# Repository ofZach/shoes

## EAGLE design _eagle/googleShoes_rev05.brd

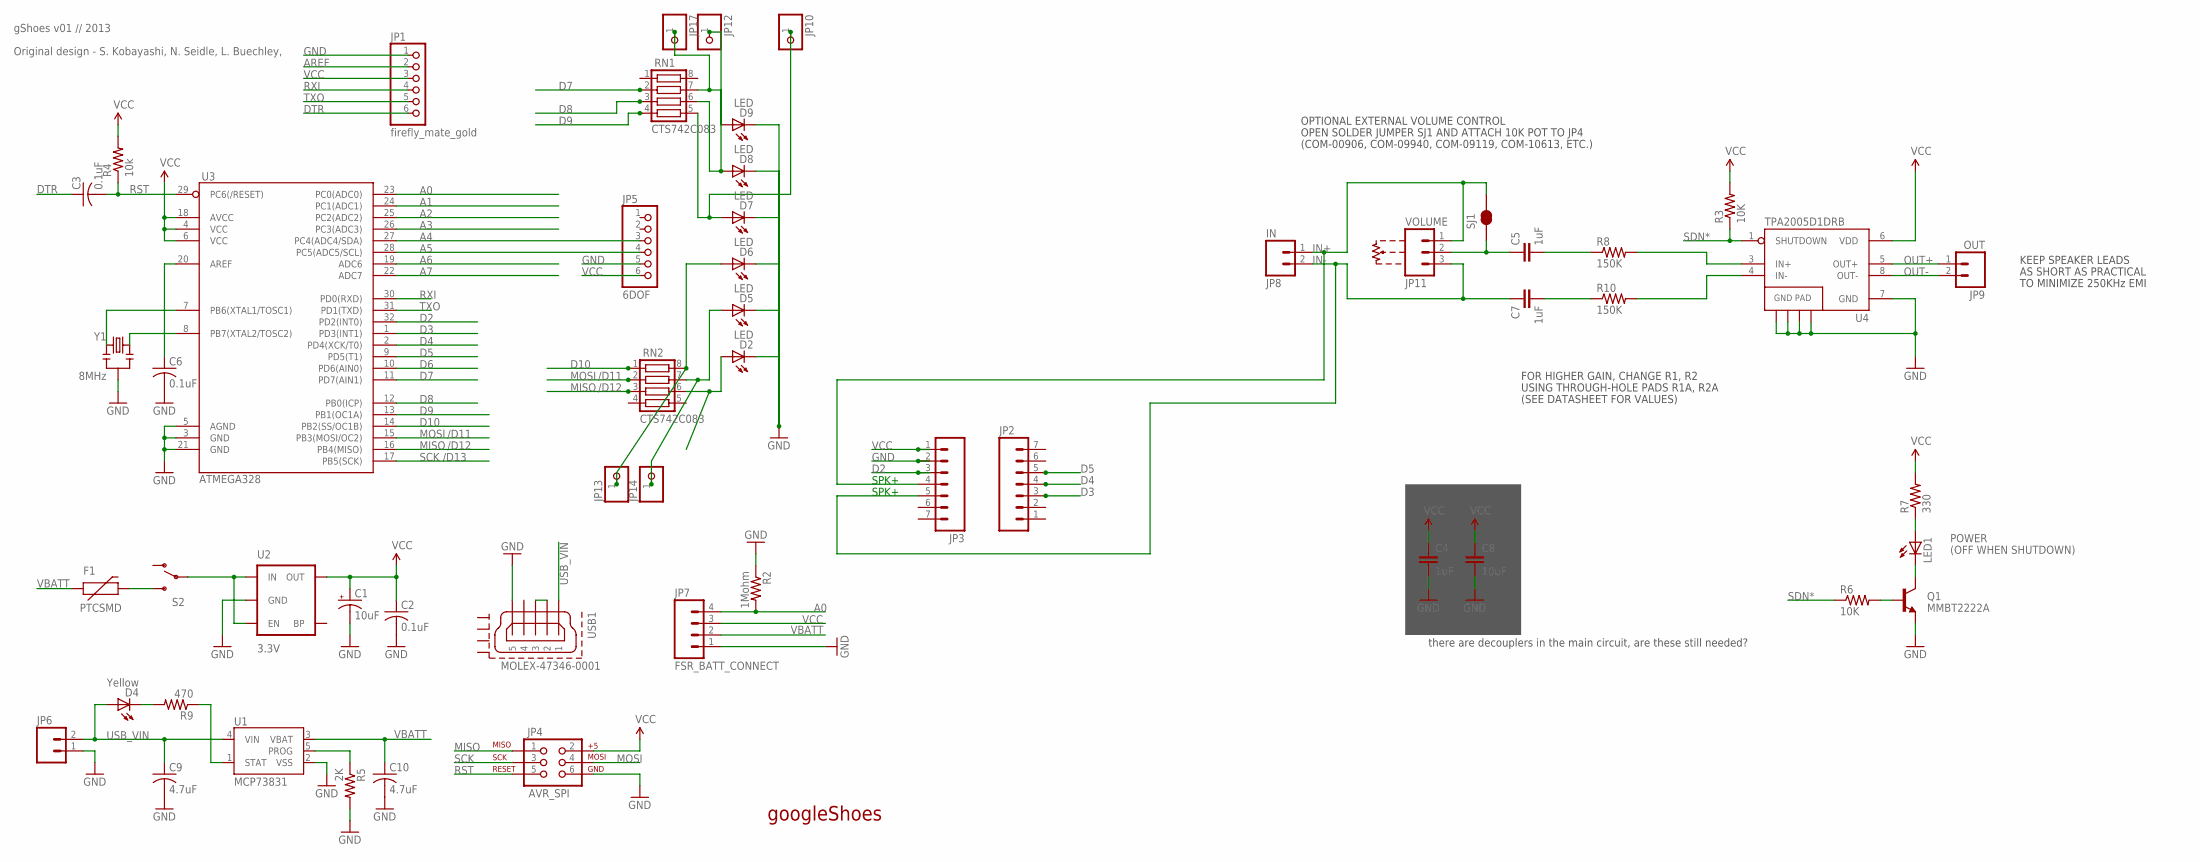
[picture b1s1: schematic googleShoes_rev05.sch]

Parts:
C1: 10uF; EIA3216
C2, C3, C6: 0.1uF; C0805
C4, C5, C7: 1uF; 1206
C8: 10uF; 1206
C9, C10: 4.7uF; C0805
D2, D5, D6, D7, D8, D9: LED; CHIP-LED0805
D4: Yellow; CHIP-LED0805
F1: PTCSMD; PTC-1206
JP1: firefly_mate_gold; 1X06-BIG
JP2, JP3: M07; 1X07
JP4: AVR_SPI; 2X3
JP5: 6DOF; 1X06-BIG
JP6: M02PTH; 1X02
JP7: FSR_BATT_CONNECT; 1X04
JP8: IN; 1X02
JP9: OUT; 1X02
JP10, JP12, JP13, JP14, JP17: PINHD-1X1CB; 1X01-CLEANBIG
JP11: VOLUME; 1X03
LED1: LEDCHIPLED_0805; CHIPLED_0805
Q1: MMBT2222A; SOT23-3
R2: 1Mohm; M0805
R3, R6: 10K; M0805
R4: 10k; M0805
R5: 2K; M0805
R7: 330; M0805
R8, R10: 150K; M0805
R9: 470; M0805
RN1, RN2: CTS742C083
S2: SWITCH-SPSTSMD; AYZ0202
SJ1: SOLDERJUMPERNC2; SJ_2S-NOTRACE
U1: MCP73831; SOT23-5
U2: 3.3V; SOT23-5
U3: ATMEGA328; TQFP32-08
U4: TPA2005D1DRB; QFN-8_PAD
USB1: MOLEX-47346-0001; MOLEX-47364-0001
Y1: 8MHz; RESONATOR-SMD

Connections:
A0: JP7.4, R2.2, U3.23 (PC0(ADC0))
A1: U3.24 (PC1(ADC1))
A2: U3.25 (PC2(ADC2))
A3: U3.26 (PC3(ADC3))
A4: JP5.3, U3.27 (PC4(ADC4/SDA))
A5: JP5.4, U3.28 (PC5(ADC5/SCL))
A6: U3.19 (ADC6)
A7: U3.22 (ADC7)
AREF: C6.1, JP1.2, U3.20 (AREF)
D2: JP3.3, U3.32 (PD2(INT0))
D3: JP2.3, U3.1 (PD3(INT1))
D4: JP2.4, U3.2 (PD4(XCK/T0))
D5: JP2.5, U3.9 (PD5(T1))
D6: U3.10 (PD6(AIN0))
D7: RN1.2, U3.11 (PD7(AIN1))
D8: RN1.3, U3.12 (PB0(ICP))
D9: RN1.4, U3.13 (PB1(OC1A))
D10: RN2.1, U3.14 (PB2(SS/OC1B))
DTR: C3.1, JP1.6
GND: C1.C (-), C2.2, C4.2, C6.2, C8.2, C9.2, C10.2, D2.C, D5.C, D6.C, D7.C, D8.C, D9.C, JP1.1, JP3.2, JP4.6, JP5.5, JP6.1, JP7.1, Q1.2 (E), R2.1, R5.2, U1.2 (VSS), U2.2 (GND), U3.3 (GND), U3.5 (AGND), U3.21 (GND), U4.7 (GND), U4.10 (GND), U4.11 (GND), U4.12 (GND), U4.13 (GND), USB1.5, Y1.2
IN+: JP3.4, JP8.1, JP11.1, SJ1.2
IN+AMP: R8.2, U4.3 (IN+)
IN-: C7.1, JP3.5, JP8.2, JP11.3
IN-AMP: R10.2, U4.4 (IN-)
MISO: JP4.1, RN2.3, U3.16 (PB4(MISO))
MOSI: JP4.4, RN2.2, U3.15 (PB3(MOSI/OC2))
unnamed: C5.1, JP11.2, SJ1.1
unnamed: D5.A, JP14.1, RN2.7
unnamed: D2.A, RN2.6
unnamed: S2.2, U2.1 (IN), U2.3 (EN)
unnamed: D6.A, JP13.1, RN2.8
unnamed: D4.C, R9.2
unnamed: F1.2, S2.3 (S)
unnamed: U3.7 (PB6(XTAL1/TOSC1)), Y1.3
unnamed: R5.1, U1.5 (PROG)
unnamed: U3.8 (PB7(XTAL2/TOSC2)), Y1.1
unnamed: R9.1, U1.1 (STAT)
unnamed: D9.A, JP17.1, RN1.7
unnamed: D8.A, JP12.1, RN1.6
unnamed: D7.A, JP10.1, RN1.5
unnamed: LED1.A, R7.1
unnamed: Q1.1 (B), R6.2
unnamed: LED1.C, Q1.3 (C)
unnamed: C5.2, R8.1
unnamed: C7.2, R10.1
unnamed: USB1.2, USB1.3
OUT+: JP9.1, U4.5 (OUT+)
OUT-: JP9.2, U4.8 (OUT-)
RST: C3.2, JP4.5, R4.1, U3.29 (PC6(/RESET))
RXI: JP1.4, U3.30 (PD0(RXD))
SCK: JP4.3, U3.17 (PB5(SCK))
SDN*: R3.1, R6.1, U4.1 (SHUTDOWN)
TXO: JP1.5, U3.31 (PD1(TXD))
USB_VIN: C9.1, D4.A, JP6.2, U1.4 (VIN), USB1.1
VBATT: C10.1, F1.1, JP7.2, U1.3 (VBAT)
VCC: C1.A (+), C2.1, C4.1, C8.1, JP1.3, JP3.1, JP4.2, JP5.6, JP7.3, R3.2, R4.2, R7.2, U2.5 (OUT), U3.4 (VCC), U3.6 (VCC), U3.18 (AVCC), U4.6 (VDD)

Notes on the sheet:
googleShoes
/D11
/D12
/D13
Original design - S. Kobayashi, N. Seidle, L. Buechley,
gShoes v01 // 2013
SPK+
POWER
(OFF WHEN SHUTDOWN)
OPEN SOLDER JUMPER SJ1 AND ATTACH 10K POT TO JP4
OPTIONAL EXTERNAL VOLUME CONTROL
FOR HIGHER GAIN, CHANGE R1, R2
USING THROUGH-HOLE PADS R1A, R2A
(SEE DATASHEET FOR VALUES)
(COM-00906, COM-09940, COM-09119, COM-10613, ETC.)
KEEP SPEAKER LEADS
AS SHORT AS PRACTICAL
TO MINIMIZE 250KHz EMI
there are decouplers in the main circuit, are these still needed?

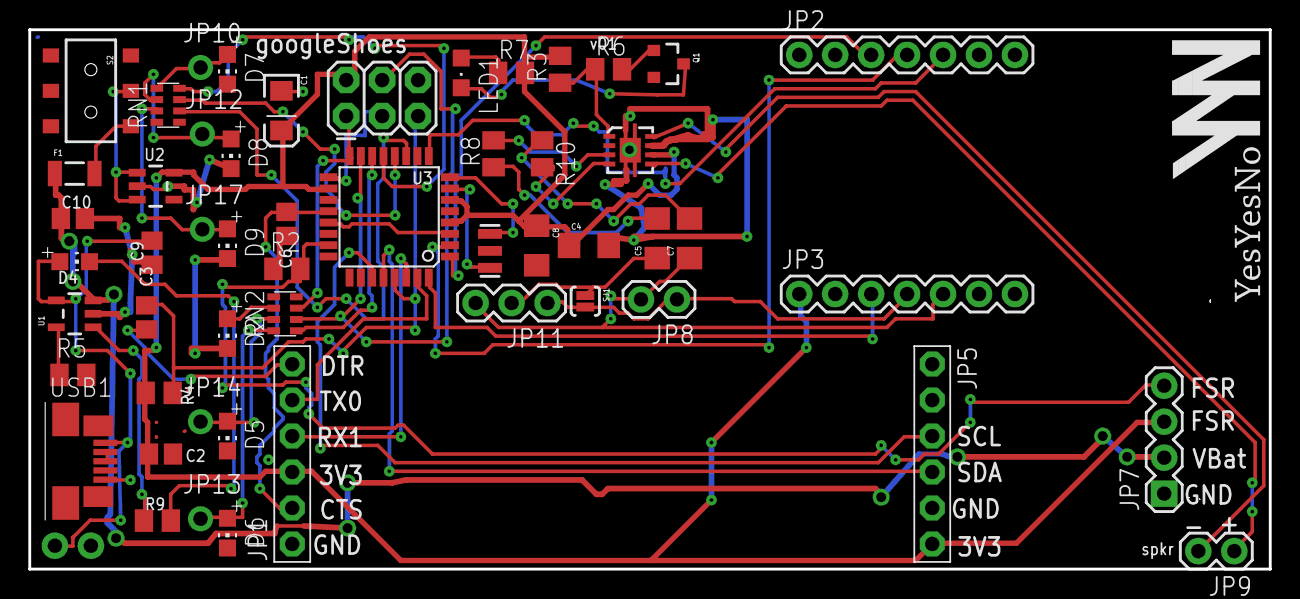
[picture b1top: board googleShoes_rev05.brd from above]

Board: 2 copper layers, 87.6 x 38.1 mm, 54 parts (1 on the bottom side), 50 nets.

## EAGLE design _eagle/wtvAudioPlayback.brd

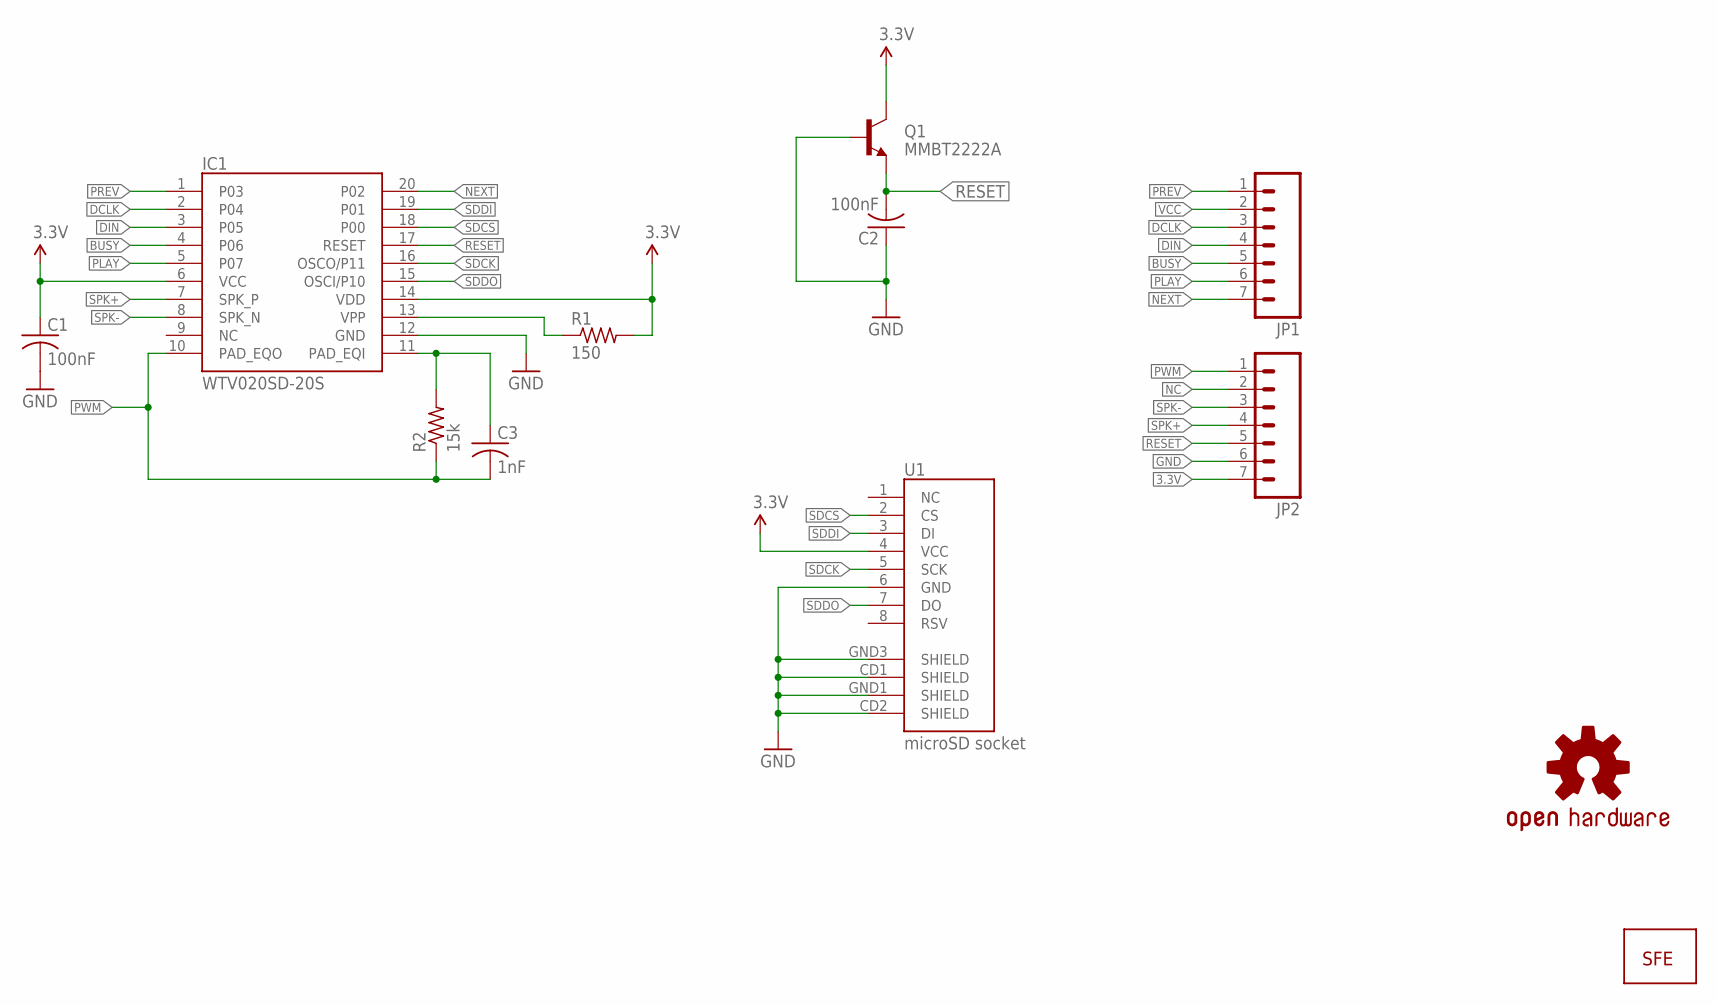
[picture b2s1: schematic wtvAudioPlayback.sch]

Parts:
C1, C2: 100nF; C025-024X044
C3: 1nF; C025-024X044
IC1: WTV020SD-20S; SSOP_20
JP1, JP2: M07; 1X07
JP5: LOGO-SFENEW; SFE-NEW-WEBLOGO
Q1: MMBT2222A; SOT23
R1: 150; 0207/2V
R2: 15k; 0207/2V
U1: microSD socket; MICRO-SD-SOCKET-PP
U$1: OSHW-LOGOS; OSHW-LOGO-S

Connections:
3.3V: C1.1, IC1.6 (VCC), IC1.14 (VDD), JP2.7, Q1.3 (C), R1.2, U1.4 (VCC)
BUSY: IC1.4 (P06), JP1.5
DCLK: IC1.2 (P04), JP1.3
DIN: IC1.3 (P05), JP1.4
GND: C1.2, C2.1, IC1.12 (GND), JP2.6, Q1.1 (B), U1.6 (GND), U1.CD1 (SHIELD), U1.CD2 (SHIELD), U1.GND1 (SHIELD), U1.GND3 (SHIELD)
unnamed: IC1.13 (VPP), R1.1
unnamed: C3.1, IC1.11 (PAD_EQI), R2.2
NC: JP2.2
NEXT: IC1.20 (P02), JP1.7
PLAY: IC1.5 (P07), JP1.6
PREV: IC1.1 (P03), JP1.1
PWM: C3.2, IC1.10 (PAD_EQO), JP2.1, R2.1
RESET: C2.2, IC1.17 (RESET), JP2.5, Q1.2 (E)
SDCK: IC1.16 (OSCO/P11), U1.5 (SCK)
SDCS: IC1.18 (P00), U1.2 (CS)
SDDI: IC1.19 (P01), U1.3 (DI)
SDDO: IC1.15 (OSCI/P10), U1.7 (DO)
SPK+: IC1.7 (SPK_P), JP2.4
SPK-: IC1.8 (SPK_N), JP2.3
VCC: JP1.2

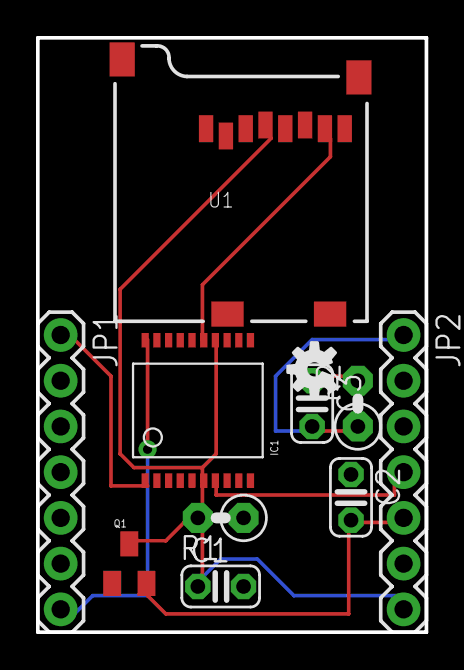
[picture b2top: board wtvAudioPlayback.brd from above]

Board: 2 copper layers, 21.6 x 33.0 mm, 12 parts (1 on the bottom side), 18 nets.

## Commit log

2013-02-22 fist commit
2013-02-22 added debugging, comments
2013-02-23 eagle files for board and audio module
2013-02-23 started routing
2013-02-24 added audio module
2013-02-24 added amplifier. needs routing.
2013-02-25 board layout
2013-02-25 routed - rev01.brd
2013-02-25 routed again- rev02
2013-02-25 pcb complete
2013-02-25 updated vbatt line, drill sizes
2013-02-25 fixed ERC errors
2013-02-26 added rawsensortest file and begin wtv mozzi integration
2013-02-26 gitignore added
2013-02-26 added OF projects

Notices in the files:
parts and their libraries:
SparkFun-Connectors: Licensing: CC v3.0 Share-Alike You are welcome to use this library for commercial purposes.
SparkFun-Aesthetics: Released under the Creative Commons
SparkFun-Aesthetics: http://creativecommons.org/licenses/by-sa/3.0
